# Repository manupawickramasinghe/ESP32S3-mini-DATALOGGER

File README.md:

# ESP32-DATALOGGER

## Overview

This repository contains the design and implementation details of three dataloggers based on the ESP32, ESP32-S3, and ESP32-S3 platforms. These devices are equipped with various peripherals and communication protocols to serve as versatile solutions for data acquisition and logging applications.

---

## Features

### Microcontroller Platforms:
1. **ESP32**
2. **ESP32-S3**
3. **ESP32-S3 with Advanced Peripherals**

### Peripherals:
- **I2C Devices:**
  - **MPU6050**: Accelerometer and Gyroscope for motion sensing.
  - **OLED Display**: For visual feedback and data visualization.
  - **BME680**: Environmental sensor for temperature, humidity, pressure, and air quality.

- **Communication Interfaces:**
  - **RS485**: For long-distance, reliable industrial communication.
  - **CAN (Controller Area Network)**: For automotive and robust communication.
  - **RS232**: Standard serial communication for various legacy devices.

- **Data Storage:**
  - **SD Card**: Local storage for data logging.

### Power Supplies:
- **230V AC to 5V DC**: Converts mains power for the device.
- **5V DC to 3.3V DC**: Supplies power to the ESP32 and low-voltage peripherals.
- **5V DC to 5V DC (Isolated)**: Provides isolated power for communication devices like RS485 and CAN.

---

## Hardware Architecture

### Block Diagram:
```text
  Mains Power (230V AC) → [230V to 5V Converter] → [5V Bus]
                                        ↘→ [5V to 3.3V Converter] → ESP32 / Peripherals
                                        ↘→ [5V to 5V Isolated Converter] → RS485 / CAN
```

### Communication Interfaces:
- **RS485, RS232, and CAN**:
  - Ensure robust and reliable communication.
  - Isolation is used to prevent electrical interference.

### Sensors and Peripherals:
- **MPU6050**: Used for motion-based applications like tilt sensing or vibration analysis.
- **OLED**: Displays real-time data or system status.
- **BME680**: Environmental monitoring for applications like weather stations or air quality measurement.

---

## Software Features

### Data Logging
- Logs data from MPU6050, BME680, and other connected sensors.
- Saves logs in CSV format on the SD card for easy analysis.

### Communication Protocols
- Transmits and receives data using RS485, RS232, and CAN interfaces.
- Configurable baud rates and communication parameters.
- Saves logs in CSV format on the SD card for easy analysis.

### OLED Display
- Displays sensor readings, status, and diagnostic information.

### Power Management
- Efficient power regulation with isolated supplies for sensitive peripherals.
- Compatible with industrial-grade power requirements.

---

## Getting Started

### Prerequisites
- Install [ESP-IDF](https://github.com/espressif/esp-idf) or [Arduino IDE](https://www.arduino.cc/) for programming the ESP32.
- Required libraries:
  - **MPU6050**: [`Adafruit_MPU6050`](https://github.com/adafruit/Adafruit_MPU6050).
  - **BME680**: [`Adafruit_BME680`](https://github.com/adafruit/Adafruit_BME680).
  - **OLED**: [`Adafruit_SSD1306`](https://github.com/adafruit/Adafruit_SSD1306).
  - **RS485, RS232, CAN**: Use drivers from ESP-IDF or third-party libraries.

### Hardware Setup
1. **Connect I2C Devices**:
   - MPU6050: Connect `SDA` and `SCL` to the respective GPIO pins.
   - OLED: Same as above, with separate I2C address.
   - BME680: Same bus as MPU6050.

2. **Set Up Communication Interfaces**:
   - RS485 and CAN require external transceivers.
   - RS232 uses UART GPIO pins.

3. **Power Supply**:
   - Use the 230V AC to 5V DC converter to power the system.
   - Ensure isolation for RS485 and CAN with the isolated 5V DC converter.

4. **Insert SD Card**:
   - Use a standard SD card formatted with FAT32.

### Hardware Design with KiCAD 8.0
Schematic and PCB Design

The schematics and PCB designs for the dataloggers are created using KiCAD 8.0. You can open the designs directly in KiCAD 8.0 to view, edit, or export them.
Opening the Project in KiCAD 8.0

-    Install KiCAD 8.0.
    Clone the repository:

    git clone https://github.com/your-repo/esp32-datalogger.git
    cd esp32-datalogger

-    Open KiCAD 8.0 and navigate to the project directory.
-   Open the .kicad_pro file to load the project.
    Use the Schematic Editor to view or modify the circuit schematic.
-    Use the PCB Editor to view or modify the PCB layout.

---

## Usage
1. Power on the device.
2. View real-time data on the OLED display.
3. Access logged data from the SD card.
4. Use RS485, RS232, or CAN for remote communication.

---

## Applications
- Environmental monitoring.
- Motion analysis.
- Industrial data acquisition.
- Communication gateways.

---

## Troubleshooting
1. **No Display on OLED**:
   - Check I2C connections and addresses.
2. **No Data on SD Card**:
   - Verify SD card format and connection.
3. **Communication Issues**:
   - Check baud rates and wiring for RS485/RS232/CAN.

---

## Contributing
Feel free to fork the repository and contribute via pull requests. Ensure changes are well-documented.

---

## License
This project is licensed under the MIT License. See `LICENSE` for details.

---

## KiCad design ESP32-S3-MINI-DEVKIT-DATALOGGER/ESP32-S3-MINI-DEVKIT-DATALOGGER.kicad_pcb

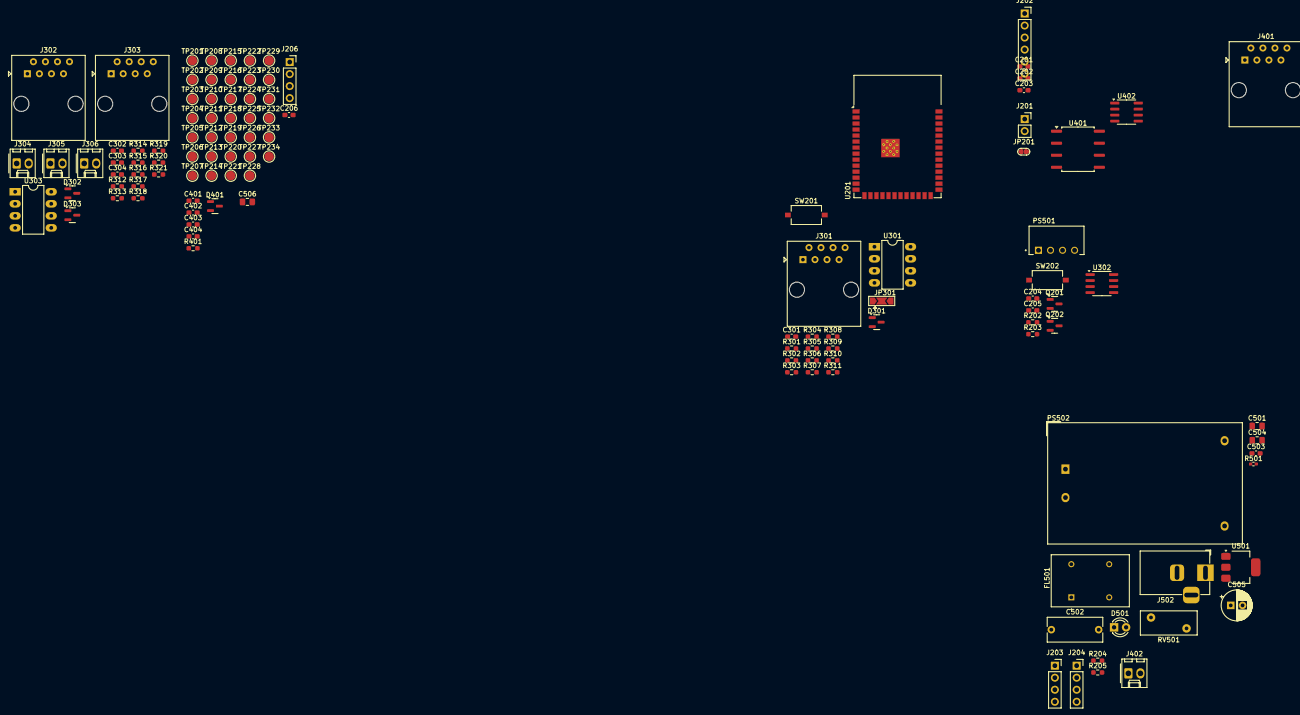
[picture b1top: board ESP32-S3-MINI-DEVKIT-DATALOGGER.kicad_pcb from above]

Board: 2 copper layers, 117 parts (0 on the bottom side), 61 nets, no tracks yet.

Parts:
C201: 1uF; C_0603_1608Metric_Pad1.08x0.95mm_HandSolder
C202: 10uF; C_0603_1608Metric_Pad1.08x0.95mm_HandSolder
C203, C205, C206, C401, C402, C403, C404: 100nF; C_0603_1608Metric_Pad1.08x0.95mm_HandSolder
C204: 0.1uF; C_0603_1608Metric_Pad1.08x0.95mm_HandSolder
C301, C302, C303, C304, C503: 0.1MFD/16V; C_0603_1608Metric_Pad1.08x0.95mm_HandSolder
C501: 10MFD/16V; C_0805_2012Metric_Pad1.18x1.45mm_HandSolder
C502: 0.1MFD/250VAC; C_Rect_L11.5mm_W5.0mm_P10.00mm_MKT
C504, C506: 0.1MFD/16V; C_0805_2012Metric_Pad1.18x1.45mm_HandSolder
C505: C_Polarized_Small_US; CP_Radial_D6.3mm_P2.50mm
D301, D302, D303, D401: SM712_SOT23; SOT-23
D501: 3mm RED; LED_D3.0mm
FL501: 10mH; B82730U3951A020
J201: Socket_01x02; PinSocket_1x02_P2.54mm_Vertical
J202: Conn_01x06_Socket; PinSocket_1x06_P2.54mm_Vertical
J203, J204, J206: Conn_01x04_Socket; PinSocket_1x04_P2.54mm_Vertical
J301, J302, J303, J401: RJ45; RJ45_Amphenol_54602-x08_Horizontal
J304, J305, J306, J402: Conn_01x02_Socket; Molex_KK-254_AE-6410-02A_1x02_P2.54mm_Vertical
J502: Barrel_Jack_Switch_Pin3Ring; BarrelJack_Horizontal
JP201: SolderJumper_2_Open; small_jumper
JP301: SolderJumper_3_Open; SolderJumper-3_P2.0mm_Open_TrianglePad1.0x1.5mm
PS501: B0505S-1WR3; CONV_B0505S-1WR3
PS502: HLK-5M05; Converter_ACDC_Hi-Link_HLK-5Mxx
Q201, Q202: MMBT3904; SOT-23
R202, R203, R204, R205: 0R_0603; R_0603_1608Metric_Pad0.98x0.95mm_HandSolder
R301, R302, R303, R304, R305, R306, R308, R309, R310, R311, R312, R313, R314, R315, R316, R317, R319, R320: 10K; R_0603_1608Metric_Pad0.98x0.95mm_HandSolder
R307, R318, R321, R401: 120R; R_0603_1608Metric_Pad0.98x0.95mm_HandSolder
R501: 1.5K; R_0402_1005Metric_Pad0.72x0.64mm_HandSolder
RV501: 10D561; RV_Disc_D12mm_W5.1mm_P7.5mm
SW201, SW202: SW_Omron_B3FS; SW_Tactile_SPST_NO_Straight_CK_PTS636Sx25SMTRLFS
TP201, TP202, TP203, TP204, TP205, TP206, TP207, TP208, TP209, TP210, TP211, TP212, TP213, TP214, TP215, TP216, TP217, TP218, TP219, TP220, TP221, TP222, TP223, TP224, TP225, TP226, TP227, TP228, TP229, TP230, TP231, TP232, TP233, TP234: TestPoint; TestPoint_Pad_D2.0mm
U201: ESP32-S3-MINI-S3-WROOM-1
U301, U303: MAX485E; DIP-8_W7.62mm_LongPads
U302: MAX3486; SOIC-8_3.9x4.9mm_P1.27mm
U401: ISO1050DUB; SOP-8_6.62x9.15mm_P2.54mm
U402: TJA1051T; SOIC-8_3.9x4.9mm_P1.27mm
U501: AMS1117-3.3; SOT-223-3_TabPin2

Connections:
3V3: C201.1, C202.1, C204.1, C206.2, C504.1, C505.1, C506.1, J203.2, J204.1, J206.1, JP301.1 (A), R204.1, R205.2, R501.1, U201.2 (3V3), U501.2 (VO)
+3.3V: C401.2, U401.1 (VCC1), U402.3 (VCC)
+5V: C402.2, C501.1, C503.1, J502.1, JP301.3 (B), PS501.2 (VIN), PS502.4 (+VO), U501.3 (VI)
/CAN_module/CAN_H: D401.1 (A1), J402.1, R401.1
/CAN_module/CAN_L: D401.2 (A2), J402.2, R401.2
/ESP32-S3-MINI-module/DTR: J202.1, Q202.2 (E), R202.1
/ESP32-S3-MINI-module/MISO: TP223.1, U201.23 (IO21)
/ESP32-S3-MINI-module/MOSI: TP225.1, U201.35 (IO42)
/ESP32-S3-MINI-module/RTS: J202.5, Q201.2 (E), R203.1
/ESP32-S3-MINI-module/SCK: TP224.1, U201.32 (IO39)
/ESP32-S3-MINI-module/SD_CS: TP226.1, U201.26 (IO45)
A1: D303.1 (A1), J301.2, J301.7, J304.1, R319.1, R321.1, U302.6 (A)
A2: D301.1 (A1), J302.2, J302.7, J305.1, R305.1, R307.1, U301.6 (A)
A3: D302.1 (A1), J303.2, J303.7, J306.1, R316.1, R318.1, U303.6 (A)
B1: D303.2 (A2), J301.1, J301.8, J304.2, R320.1, R321.2, U302.7 (B)
B2: D301.2 (A2), J302.1, J302.8, J305.2, R306.1, R307.2, U301.7 (B)
B3: D302.2 (A2), J303.1, J303.8, J306.2, R317.1, R318.2, U303.7 (B)
DE-485: R302.1, R309.1, R313.1, U301.3 (DE), U302.3 (DE), U303.3 (DE)
EN: JP201.1 (A), Q201.3 (C), TP233.1, U201.3 (EN)
GND: C201.2, C202.2, C203.2, C204.2, C205.1, C206.1, C301.2, C302.2, C303.2, C304.2, C401.1, C402.1, C501.2, C503.2, C504.2, C505.2, C506.2, D301.3 (common), D302.3 (common), D303.3 (common), D401.3 (common), D501.1 (K), J201.2, J202.6, J203.1, J204.2, J206.2, J301.3, J301.6, J302.3, J302.6, J303.3, J303.6, J502.2, J502.3, PS501.1 (GND), PS502.3 (-VO), R306.2, R317.2, R320.2, SW201.2, SW202.2, U201.1 (GND), U201.40 (GND), U201.41 (GND), U301.5 (GND), U302.5 (GND), U303.5 (GND), U401.4 (GND1), U402.2 (GND), U501.1 (GND)
IO1: TP201.1, U201.39 (IO1)
IO2: TP202.1, U201.38 (IO2)
IO3: TP203.1, U201.15 (IO3)
IO4: TP204.1, U201.4 (IO4)
IO5: TP205.1, U201.5 (IO5)
IO6: TP206.1, U201.6 (IO6)
IO7: TP207.1, U201.7 (IO7)
IO8: TP208.1, U201.12 (IO8)
IO9: TP209.1, U201.17 (IO9)
IO10: TP210.1, U201.18 (IO10)
IO11: TP211.1, U201.19 (IO11)
IO12: TP212.1, U201.20 (IO12)
IO13: TP213.1, U201.21 (IO13)
IO14: TP214.1, U201.22 (IO14)
IO15: TP215.1, U201.8 (IO15)
IO16: TP216.1, U201.9 (IO16)
IO38: TP227.1, U201.31 (IO38)
IO40: TP228.1, U201.33 (IO40)
IO41: TP229.1, U201.34 (IO41)
IO46: TP230.1, U201.16 (IO46)
ISO_5V: C403.2, C404.2, PS501.4 (+VO), U401.8 (VCC2)
ISO_GND: C403.1, C404.1, PS501.3 (0V), U401.5 (GND2)
unnamed: C502.1, FL501.2, RV501.2
unnamed: D501.2 (A), R501.2
unnamed: C502.2, FL501.1, RV501.1
unnamed: C203.1, JP201.2 (B), SW201.1
unnamed: FL501.3, PS502.1 (AC_1)
unnamed: FL501.4, PS502.2 (AC_2)
unnamed: Q201.1 (B), R202.2
unnamed: Q202.1 (B), R203.2
RE-485: R303.1, R310.1, R314.1, U301.2 (~RE), U302.2 (~RE), U303.2 (~RE)
RS485_VCC: C301.1, C302.1, C303.1, C304.1, JP301.2 (C), R301.2, R302.2, R303.2, R304.2, R305.2, R308.2, R309.2, R310.2, R311.2, R312.2, R313.2, R314.2, R315.2, R316.2, R319.2, U301.8 (VCC), U302.8 (VCC), U303.8 (VCC)
RST: C205.2, J201.1, Q202.3 (C), SW202.1, TP234.1, U201.27 (IO0)
RX-485: R304.1, R311.1, R315.1, TP220.1, U201.11 (IO18), U301.1 (RO), U302.1 (RO), U303.1 (RO)
SCL: J203.3, J204.3, J206.3, R204.2, TP231.1, U201.24 (IO47)
SDA: J203.4, J204.4, J206.4, R205.1, TP232.1, U201.25 (IO48)
TX-485: R301.1, R308.1, R312.1, TP219.1, U201.10 (IO17), U301.4 (DI), U302.4 (DI), U303.4 (DI)
UART0RX: J202.3, TP218.1, U201.36 (RXD0)
UART0TX: J202.2, TP217.1, U201.37 (TXD0)
USB +: TP221.1, U201.13 (IO19)
USB -: TP222.1, U201.14 (IO20)

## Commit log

2023-07-20 First DEV commit
2024-05-05 Basic Structure made, need more refining and parts
    Add the Filtering to the CAN and RS485, If make money this month
2025-01-02 Small Changes
    Adding I2C components
    More RS485
    And it is required changing the Labels for RS485 . for 3 different channels
    And Make them ISO Pins
2025-01-02 Adding ESP32 and ESP32S3 PCBs as well
2025-01-02 Adding ESP32S3 Board
2025-01-02 Changes to Readme
